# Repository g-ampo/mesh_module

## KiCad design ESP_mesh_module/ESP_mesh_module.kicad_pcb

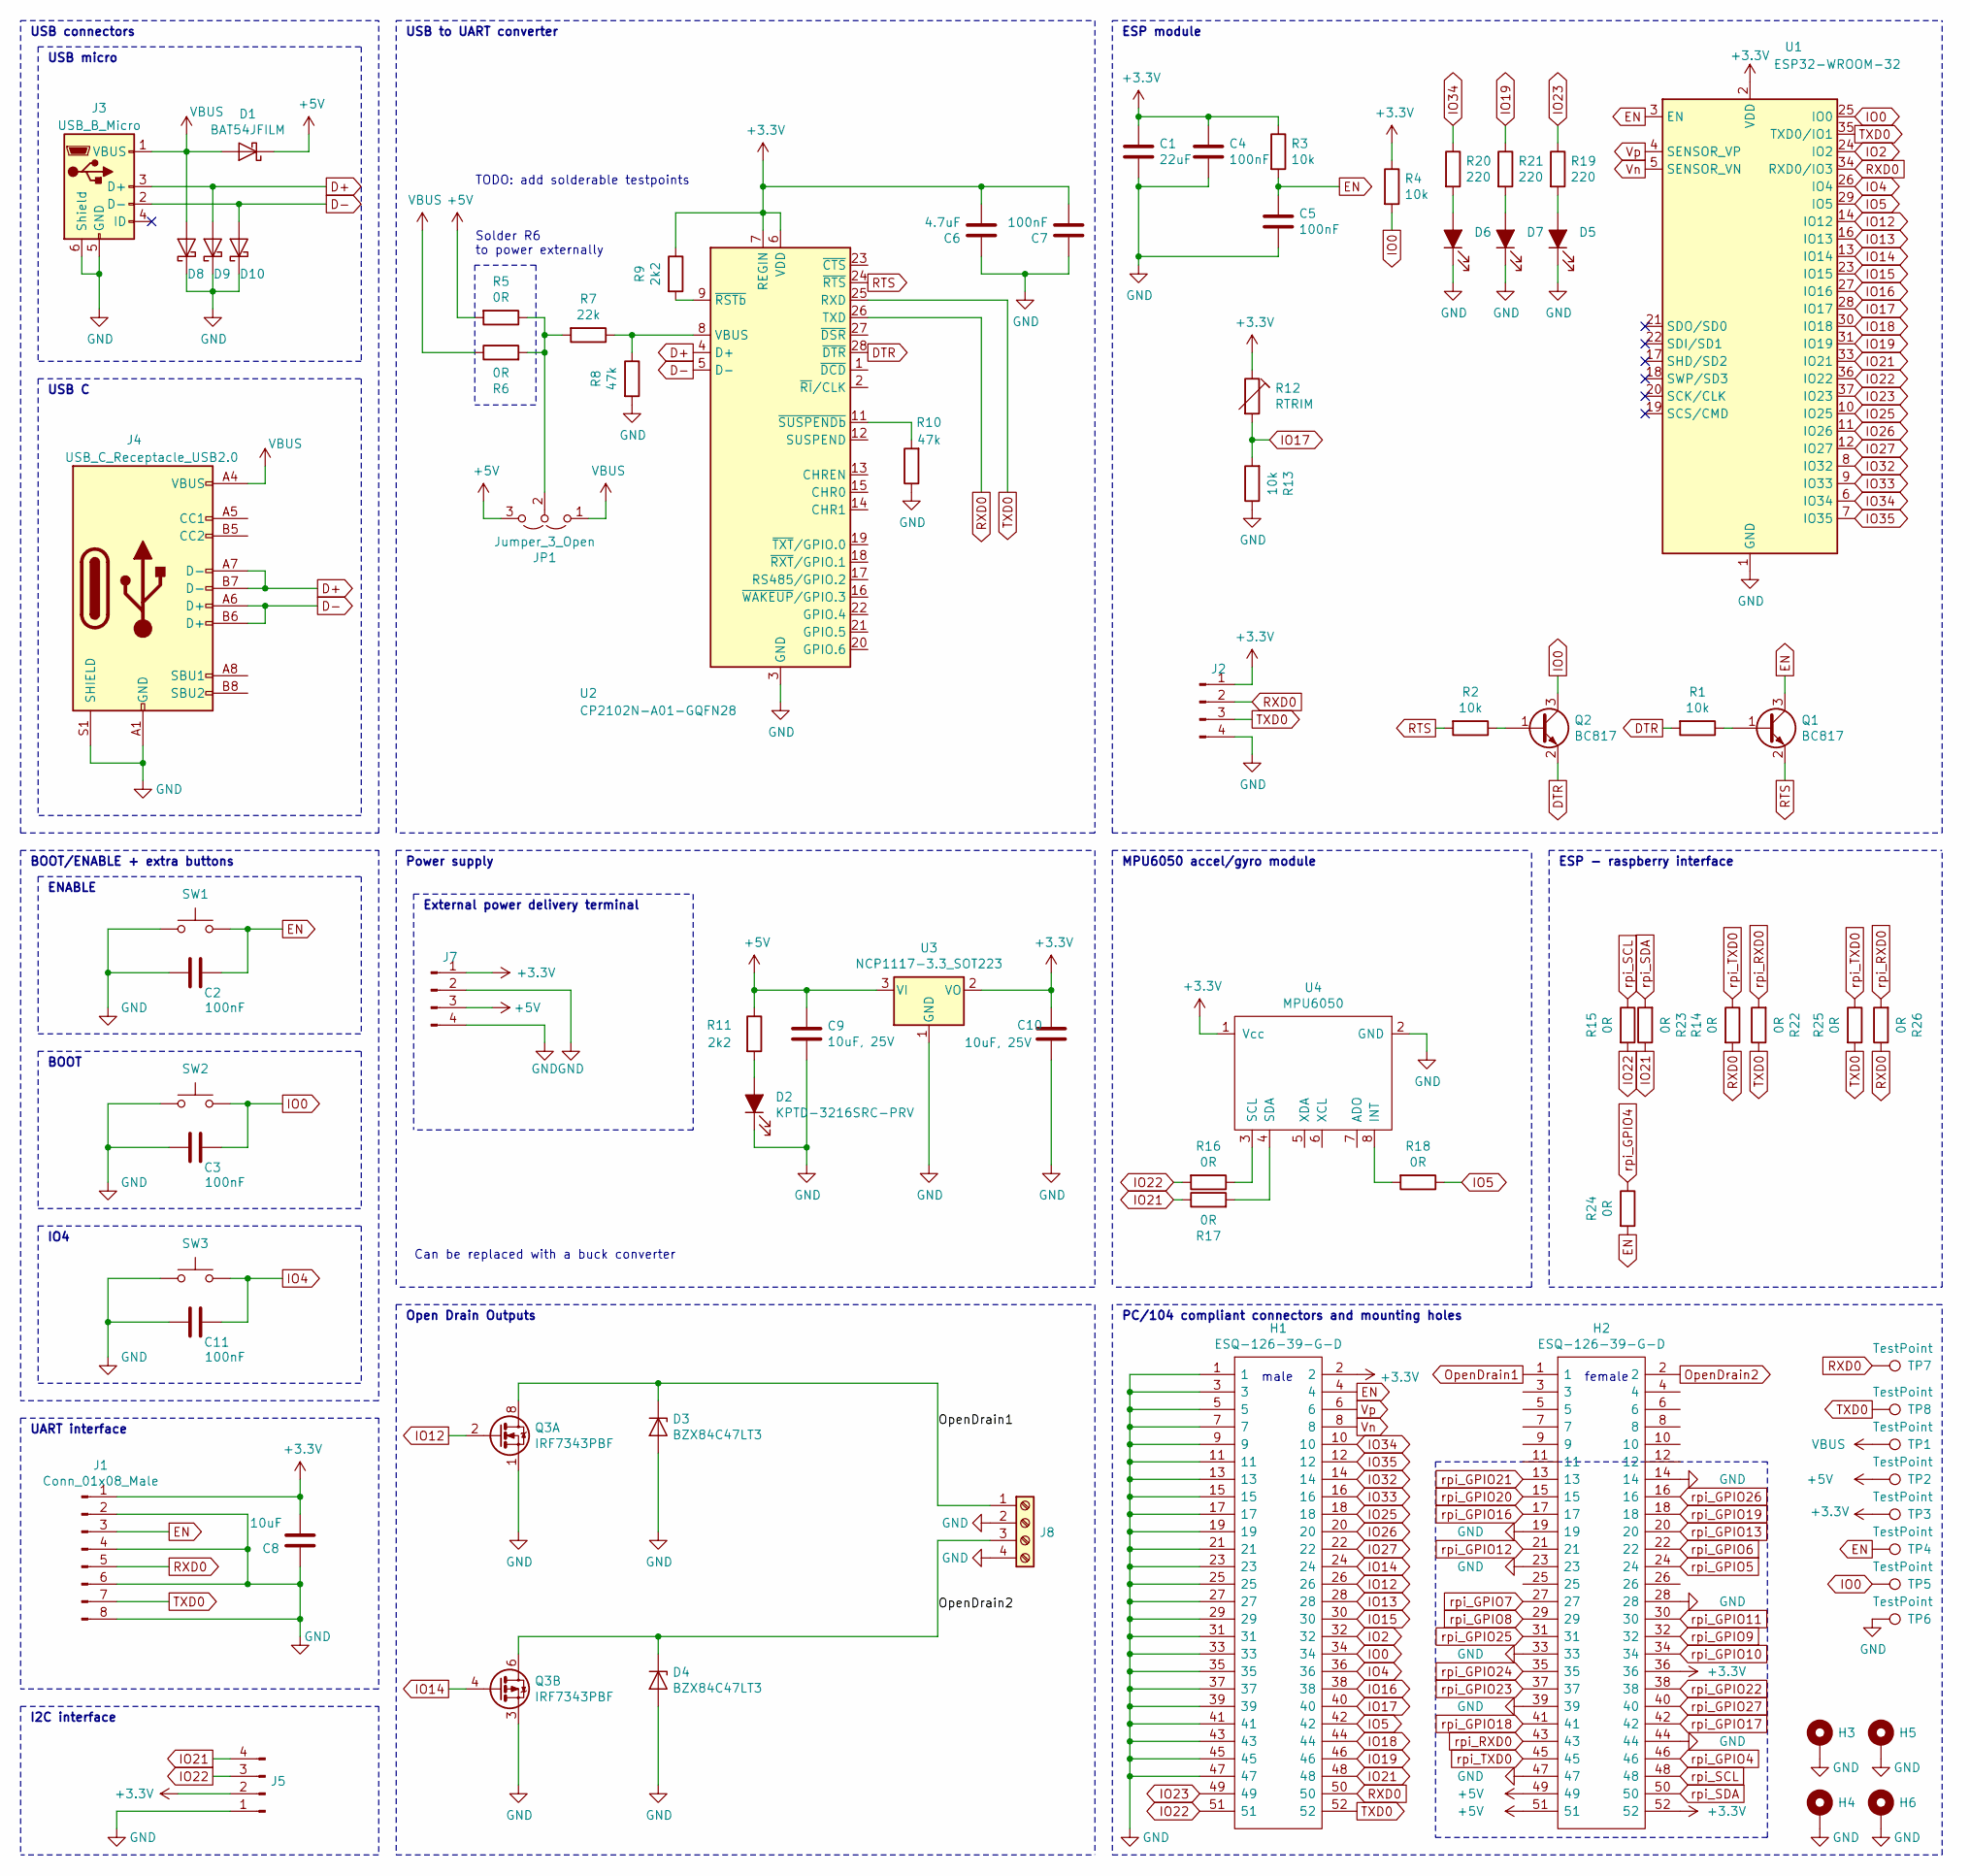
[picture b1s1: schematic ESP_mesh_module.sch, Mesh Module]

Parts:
C1: 22uF; R_0805_2012Metric; LCSC C5674
C2, C3, C4, C5, C7, C11: 100nF; R_0805_2012Metric; LCSC C360619
C6: 4.7uF; R_0805_2012Metric; LCSC C1779
C8: 10uF; R_0805_2012Metric; LCSC C17024
C9, C10: 10uF, 25V; R_0805_2012Metric; LCSC C17024
D1: BAT54JFILM; D_SOD-323_HandSoldering
D2, D5, D6, D7: KPTD-3216SRC-PRV; LED_1206_3216Metric; LCSC C598387
D3, D4: BZX84C47LT3; D_SOT-23_ANK; LCSC C118591
D8, D9, D10: PESD5V0L 1BA; D_SOD-323_HandSoldering; LCSC C85380
H1, H2: ESQ-126-39-G-D; SHDR52W64P254_2X26_6550X495X1384P; Manufacturer_Part_Number ESQ-126-39-G-D; Mouser Part Number 200-ESQ12639GD
H3, H4, H5, H6: MountingHole_Pad; Mounting_hole_PC104
J1: Conn_01x08_Male; IDC-Header_2x04_P2.54mm_Vertical
J2, J5, J7: Conn_01x04_Male; PinHeader_1x04_P2.54mm_Vertical
J3: USB_B_Micro; USB_Micro-B_Molex_47346-0001
J4: USB_C_Receptacle_USB2.0
J8: Screw_Terminal_01x04; PinHeader_1x04_P2.54mm_Vertical
JP1: Jumper_3_Open; PinHeader_1x03_P2.54mm_Vertical
Q1, Q2: BC817; SOT-23; LCSC C52801
Q3: IRF7343PBF; SOIC-8_3.9x4.9mm_P1.27mm; LCSC C558150
R1, R2, R4: 10k; R_0805_2012Metric; LCSC C115295
R3: 10k; R_0805_2012Metric
R5, R6, R14, R15, R16, R17, R18, R22, R23, R24, R25, R26: 0R; R_0805_2012Metric; LCSC C702869
R7: 22k; R_0805_2012Metric; LCSC C139902
R8, R10: 47k; R_0805_2012Metric; LCSC C139872
R9, R11: 2k2; R_0805_2012Metric; LCSC C26017
R12: RTRIM; Potentiometer_Piher_PT-6-V_Vertical
R13: 10k; R_Axial_DIN0207_L6.3mm_D2.5mm_P7.62mm_Horizontal
R19, R20, R21: 220; R_0805_2012Metric; LCSC C165202
SW1, SW2, SW3: SW_Push; SW_PUSH_6mm
TP1, TP2, TP3, TP4, TP5, TP6, TP7, TP8: TestPoint; TestPoint_Pad_D1.5mm
U1: ESP32-WROOM-32; LCSC C82899
U2: CP2102N-A01-GQFN28; QFN-28-1EP_5x5mm_P0.5mm_EP3.35x3.35mm; LCSC C6568
U3: NCP1117-3.3_SOT223; SOT-223-3_TabPin2; LCSC C146799
U4: MPU6050

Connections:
+3V3: C1.1, C4.1, C6.2, C7.2, C8.2, C10.1, H1.2, H2.36, H2.52, J1.1, J2.1, J5.2, J7.1, R3.1, R4.1, R9.1, R12.1, TP3.1, U1.2 (VDD), U2.6 (VDD), U2.7 (REGIN), U3.2 (VO), U4.1 (Vcc)
+5V: C9.1, D1.1 (K), H2.49, H2.51, J7.3, JP1.3 (B), R5.2, R11.1, TP2.1, U3.3 (VI)
D+: D9.2 (A), J3.3 (D+), J4.A7 (D-), J4.B7 (D-), U2.4 (D+)
D-: D10.2 (A), J3.2 (D-), J4.A6 (D+), J4.B6 (D+), U2.5 (D-)
DTR: Q2.2 (E), R1.2, U2.28 (~DTR)
EN: C2.1, C5.1, H1.4, J1.3, Q1.3 (C), R3.2, R24.2, SW1.2, TP4.1, U1.3 (EN)
GND: C1.2, C2.2, C3.2, C4.2, C5.2, C6.1, C7.1, C8.1, C9.2, C10.2, C11.2, D2.1 (K), D3.2 (A), D4.2 (A), D5.1 (K), D6.1 (K), D7.1 (K), D8.1 (K), D9.1 (K), D10.1 (K), H1.1, H1.3, H1.5, H1.7, H1.9, H1.11, H1.13, H1.15, H1.17, H1.19, H1.21, H1.23, H1.25, H1.27, H1.29, H1.31, H1.33, H1.35, H1.37, H1.39, H1.41, H1.43, H1.45, H1.47, H2.14, H2.19, H2.23, H2.28, H2.33, H2.39, H2.44, H2.47, H3.1, H4.1, H5.1, H6.1, J1.2, J1.4, J1.6, J1.8, J2.4, J3.5 (GND), J3.6 (Shield), J4.A1 (GND), J4.A12 (GND), J4.B1 (GND), J4.B12 (GND), J4.S1 (SHIELD), J5.1, J7.2, J7.4, J8.2, J8.4, Q3.1 (S), Q3.3 (1), R8.2, R10.1, R13.1, SW1.1, SW2.1, SW3.1, TP6.1, U1.1 (GND), U1.15 (GND), U1.38 (GND), U1.39, U2.3 (GND), U2.29 (GND), U3.1 (GND), U4.2 (GND)
IO0: C3.1, H1.34, Q2.3 (C), R4.2, SW2.2, TP5.1, U1.25 (IO0)
IO2: H1.32, U1.24 (IO2)
IO4: C11.1, H1.36, SW3.2, U1.26 (IO4)
IO5: H1.42, R18.1, U1.29 (IO5)
IO12: H1.26, Q3.2 (G), U1.14 (IO12)
IO13: H1.28, U1.16 (IO13)
IO14: H1.24, Q3.4 (G), U1.13 (IO14)
IO15: H1.30, U1.23 (IO15)
IO16: H1.38, U1.27 (IO16)
IO17: H1.40, R12.2, R13.2, U1.28 (IO17)
IO18: H1.44, U1.30 (IO18)
IO19: H1.46, R21.1, U1.31 (IO19)
IO21: H1.48, J5.4, R17.1, R23.1, U1.33 (IO21)
IO22: H1.51, J5.3, R15.2, R16.2, U1.36 (IO22)
IO23: H1.49, R19.1, U1.37 (IO23)
IO25: H1.18, U1.10 (IO25)
IO26: H1.20, U1.11 (IO26)
IO27: H1.22, U1.12 (IO27)
IO32: H1.14, U1.8 (IO32)
IO33: H1.16, U1.9 (IO33)
IO34: H1.10, R20.1, U1.6 (IO34)
IO35: H1.12, U1.7 (IO35)
unnamed: D2.2 (A), R11.2
unnamed: D5.2 (A), R19.2
unnamed: D6.2 (A), R20.2
unnamed: D7.2 (A), R21.2
unnamed: JP1.2 (C), R5.1, R6.2, R7.2
unnamed: Q1.1 (B), R1.1
unnamed: Q2.1 (B), R2.1
unnamed: R7.1, R8.1, U2.8 (VBUS)
unnamed: R9.2, U2.9 (~RSTb)
unnamed: R10.2, U2.11 (~SUSPENDb)
unnamed: R16.1, U4.3 (SCL)
unnamed: R17.2, U4.4 (SDA)
unnamed: R18.2, U4.8 (INT)
OpenDrain1: D3.1 (K), H2.1, J8.1, Q3.7 (D), Q3.8 (D)
OpenDrain2: D4.1 (K), H2.2, J8.3, Q3.5 (D), Q3.6 (D)
RTS: Q1.2 (E), R2.2, U2.24 (~RTS)
RXD0: H1.50, J1.5, J2.2, R14.2, R26.1, TP7.1, U1.34 (RXD0/IO3), U2.26 (TXD)
TXD0: H1.52, J1.7, J2.3, R22.1, R25.2, TP8.1, U1.35 (TXD0/IO1), U2.25 (RXD)
VBUS: D1.2 (A), D8.2 (A), J3.1 (VBUS), J4.A4 (VBUS), J4.A9 (VBUS), J4.B4 (VBUS), J4.B9 (VBUS), JP1.1 (A), R6.1, TP1.1
Vn: H1.8, U1.5 (SENSOR_VN)
Vp: H1.6, U1.4 (SENSOR_VP)
rpi_GPIO4: H2.46, R24.1
rpi_GPIO5: H2.24
rpi_GPIO6: H2.22
rpi_GPIO7: H2.27
rpi_GPIO8: H2.29
rpi_GPIO9: H2.32
rpi_GPIO10: H2.34
rpi_GPIO11: H2.30
rpi_GPIO12: H2.21
rpi_GPIO13: H2.20
rpi_GPIO16: H2.17
rpi_GPIO17: H2.42
rpi_GPIO18: H2.41
rpi_GPIO19: H2.18
rpi_GPIO20: H2.15
rpi_GPIO21: H2.13
rpi_GPIO22: H2.38
rpi_GPIO23: H2.37
rpi_GPIO24: H2.35
rpi_GPIO25: H2.31
rpi_GPIO26: H2.16
rpi_GPIO27: H2.40
rpi_RXD0: H2.43, R22.2, R26.2
rpi_SCL: H2.48, R15.1
rpi_SDA: H2.50, R23.2
rpi_TXD0: H2.45, R14.1, R25.1

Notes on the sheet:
USB connectors
ESP module
TODO: add solderable testpoints
Solder R6 to power externally
USB to UART converter
USB micro
USB C
MPU6050 accel/gyro module
PC/104 compliant connectors and mounting holes
Open Drain Outputs
BOOT
ENABLE
Can be replaced with a buck converter
External power delivery terminal
Power supply
UART interface
BOOT/ENABLE + extra buttons
IO4
I2C interface
female
male
ESP - raspberry interface

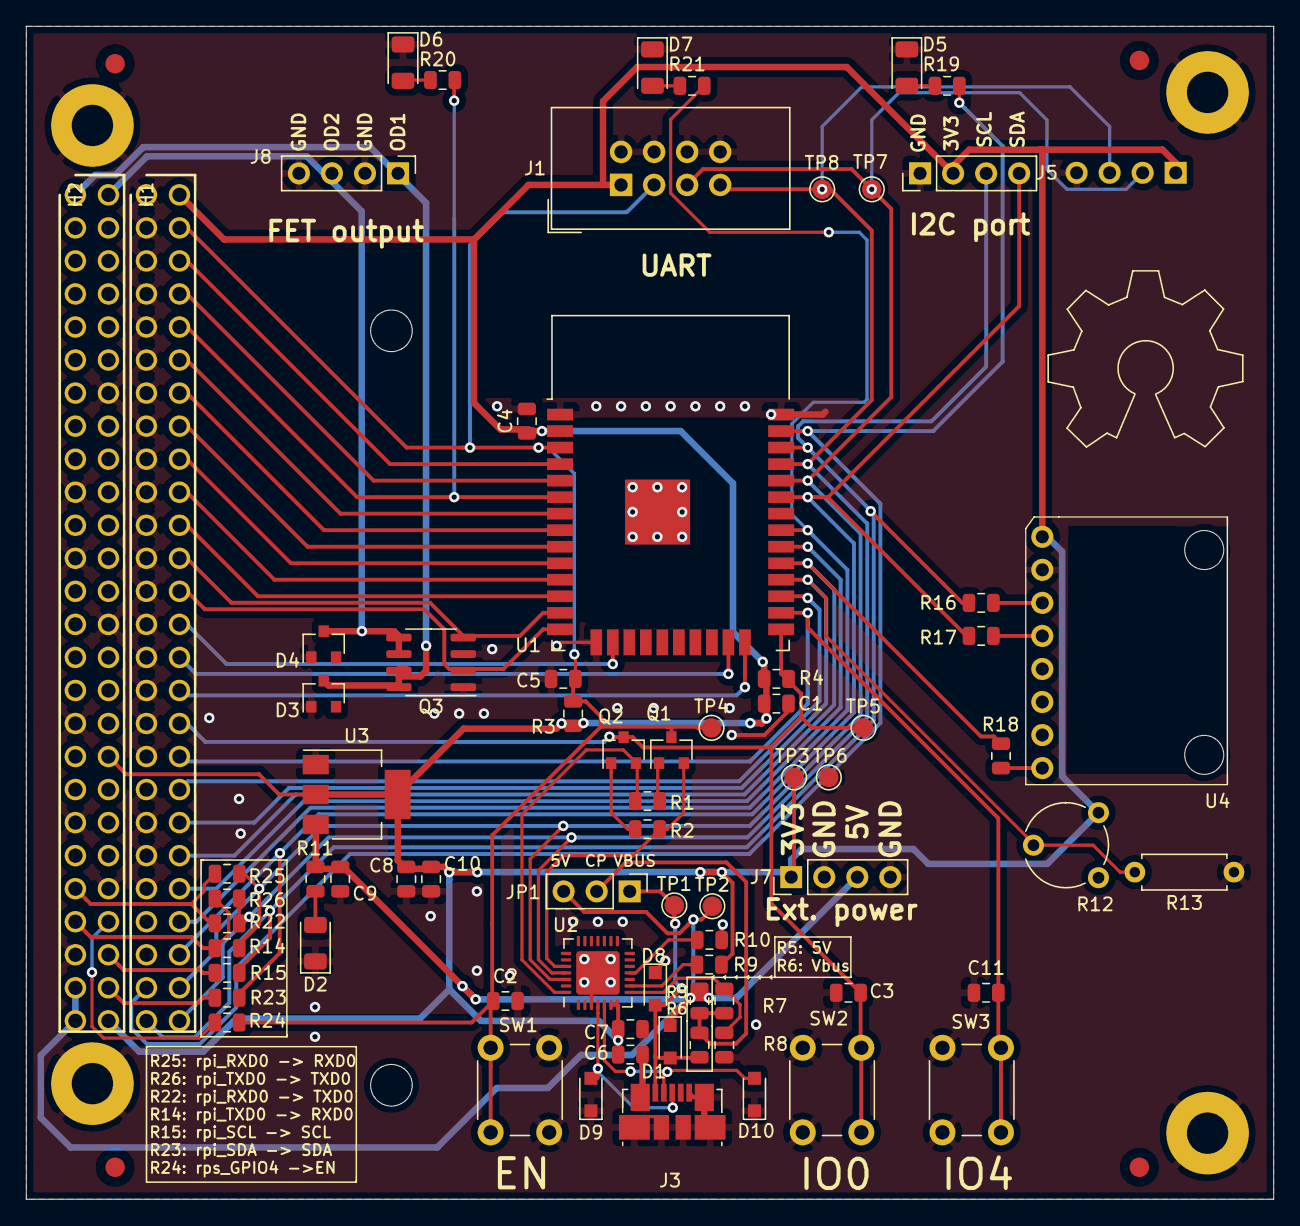
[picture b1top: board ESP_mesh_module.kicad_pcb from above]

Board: 2 copper layers, 95.9 x 90.2 mm, 80 parts (1 on the bottom side), 55 nets.

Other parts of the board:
rpi_mount: MountingHole_3.2mm_M3
rpi_mount#2: MountingHole_3.2mm_M3

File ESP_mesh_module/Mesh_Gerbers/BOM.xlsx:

Comment | Designator | Footprint | LCSC Part #
BAT54JFILM | D1 | SOT-323 | C86299 | -
BC817 | Q1, Q2 | SOD-23 | C52801 | -
10k | R1, R2, R3, R4 | 0805_R | C115295 | -
CP2102N-A01 | U2 | QFN-28 | C6568 | -
2k2 | R9, R11 | 0805_R | C26017 | -
22k | R7 | 0805_R | C139902 | -
47k | R8, R10 | 0805_R | C139872 | -
0R | R6, R5, R14, R15, R16, R17, R18, R22, R23, R24, R25, R26 | 0805_R | C702869 | -
PESD5V0L 1BA | D8, D9, D10 | SOD-323 | C85380 | -
100nF | C2, C3, C4, C5, C7, C11 | 0805_C | C360619 | -
4.7uF, 25V | C6 | 0805_C | C1779 | -
22uF, 25V | C1 | 0805_C | C5674 | -
ESP32-WROOM-32 | U1 | WiFi Module | C6568 | -
220 | R19, R20, R21 | 0805_R | C165202 | -
BZX84C47LT3 | D3, D4 | SOT-23 | C118591 | -
IRF7343PBF | Q3 | SOIC-8 | C558150
NCP1117-3.3 | U3 | SOT-223 | C146799 | -
10uF, 16V | C8, C9, C10 | 0805_C | C17024 | -
KPTD-3216SRC-PRV | D2, D5, D6, D7 | 1206_LED | C598387 | -
